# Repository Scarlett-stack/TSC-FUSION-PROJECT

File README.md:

# TSC-FUSION-PROJECT
Ebook project TSC 2025
## Schema bloc

## BOM
| Componentă                                 | Link sursă                                                                                          | Datasheet                                                                                          |
|--------------------------------------------|------------------------------------------------------------------------------------------------------|-----------------------------------------------------------------------------------------------------|
| BME680                                     | [SnapEDA](https://www.snapeda.com/parts/BME680/Bosch/view-part/?welcome=home)                      | [Datasheet](https://www.snapeda.com/parts/BME680/Bosch%20Sensortec/datasheet/)                    |
| CC0402MRX5R5BB106                          | [ComponentSearchEngine](https://componentsearchengine.com/part-view/CC0402MRX5R5BB106/YAGEO)       | [Datasheet](https://componentsearchengine.com/Datasheets/2/CC0402MRX5R5BB106.pdf)                 |
| DMG2305UX-7                                | [ComponentSearchEngine](https://componentsearchengine.com/part-view/DMG2305UX-7/Diodes%20Incorporated) | [Datasheet](https://www.diodes.com//assets/Datasheets/DMG2305UX.pdf)                              |
| Varistor B72520T0350K062                   | [Mouser](https://www.mouser.co.uk/ProductDetail/EPCOS-TDK/B72520T0350K062?qs=dEfas%2FXlABIszF52uu7vrg%3D%3D) | [Datasheet](https://www.tdk-electronics.tdk.com/inf/75/db/CTVS_14/Surge_protection_series.pdf)   |
| FH34SRJ-24S-0.5SH_99_                      | [ComponentSearchEngine](https://componentsearchengine.com/part-view/XC6220A331MR-G/Torex)          | [Datasheet](https://product.torexsemi.com/system/files/series/xc6220.pdf)                         |
| MAX17048G+T10                              | [SnapEDA](https://www.snapeda.com/parts/MAX17048G+T10/Analog+Devices/view-part/?ref=eda)           | [Datasheet](https://www.snapeda.com/parts/MAX17048G+T10/Analog%20Devices/datasheet/)              |
| MBR0530                                    | [Mouser](https://ro.mouser.com/ProductDetail/KYOCERA-AVX/SD0805S020S1R0?qs=jCA%252BPfw4LHbpkAoSnwrdjw%3D%3D) | [Datasheet](https://ro.mouser.com/datasheet/2/40/schottky-3165252.pdf)                            |
| PGB1010603MR                               | [SnapEDA](https://www.snapeda.com/parts/PGB1010603MR/Littelfuse/view-part/?ref=eda)                | [Datasheet](https://www.snapeda.com/parts/PGB1010603MR/Littelfuse%20Inc./datasheet/)              |
| TR3B106K025C1300                           | [Mouser](https://ro.mouser.com/ProductDetail/Vishay-Sprague/TR3B106K025C1300?qs=jCGqFXxTmLdffnuDkXzk1g%3D%3D) | [Datasheet](https://www.vishay.com/docs/40080/tr3.pdf)                                            |
| USB4110-GF-A                               | [ComponentSearchEngine](https://componentsearchengine.com/part-view/USB4110-GF-A/GCT%20(GLOBAL%20CONNECTOR%20TECHNOLOGY)) | [Datasheet](https://gct.co/files/drawings/usb4110.pdf)                                            |
| SI1308EDL-T1-GE3                           | [ComponentSearchEngine](https://componentsearchengine.com/part-view/SI1308EDL-T1-GE3/Vishay)       | [Datasheet](https://componentsearchengine.com/Datasheets/1/SI1308EDL-T1-GE3.pdf)                  |
| Solder Jumper (SJ)                         | [GrabCAD](https://grabcad.com/library/solder-jumpers-1)                                             | —                                                                                                  |
| USBLC6-2SC6Y                               | [SnapEDA](https://www.snapeda.com/parts/USBLC6-2SC6Y/STMicroelectronics/view-part/?ref=eda)        | [Datasheet](https://www.snapeda.com/parts/USBLC6-2SC6Y/STMicroelectronics/datasheet/)             |
| W25Q512JVEIQ                               | [SnapEDA](https://www.snapeda.com/parts/W25Q512JVEIQ/Winbond+Electronics/view-part/?ref=eda)       | [Datasheet](https://www.snapeda.com/parts/W25Q512JVEIQ/Winbond%20Electronics/datasheet/)          |
| XC6220A331MR-G                             | [ComponentSearchEngine](https://componentsearchengine.com/part-view/XC6220A331MR-G/Torex)          | [Datasheet](https://product.torexsemi.com/system/files/series/xc6220.pdf)                         |
| RC0402FR-07226RL                           | [SnapEDA](https://www.snapeda.com/parts/RC0402FR-07226RL/Yageo/view-part/)                         | [Datasheet](https://www.snapeda.com/parts/RC0402FR-07226RL/Yageo/datasheet/)                      |
| QWIIC PRT-14417                            | [SnapEDA](https://www.snapeda.com/parts/PRT-14417/SparkFun/view-part/)                             | [Datasheet](https://www.snapeda.com/parts/PRT-14417/SparkFun%20Electronics/datasheet/)            |
| BUTTON EVQPUJ02K                           | [Panasonic](https://industry.panasonic.com/global/en/downloads?tab=cad&small_g_cd=203&part_no=EVQPUJ02K) | [Datasheet](https://industry.panasonic.com/global/en/downloads?tab=catalog&small_g_cd=203&part_no=EVQPUJ02K) |
| CPH3225A                                   | [SnapEDA](https://www.snapeda.com/parts/CPH3225A/Seiko+Instruments/view-part/?ref=eda)             | [Datasheet](https://www.snapeda.com/parts/CPH3225A/Seiko%20Instruments/datasheet/)                |
| KP-1608SURCK (LED 0603)                    | [SnapEDA](https://www.snapeda.com/parts/KP-1608SURCK/Kingbright/view-part/?ref=search&t=LED%200603) | [Datasheet](https://www.snapeda.com/parts/KP-1608SURCK/Kingbright/datasheet/)                     |
| 112A-TAAR-R03_ATTEND                       | [Comet](https://store.comet.bg/en/Catalogue/Product/43497/)                                        | [Datasheet](https://store.comet.bg/en/Catalogue/Product/43497/)                                   |
| 744043680                                  | [DigiKey](https://www.digikey.sg/en/models/1638515)                                                 | [Datasheet](https://www.we-online.com/components/products/datasheet/744043680.pdf)                |
| BD5229G-TR                                 | [ComponentSearchEngine](https://componentsearchengine.com/part-view/BD5229G-TR/ROHM%20Semiconductor) | [Datasheet](https://datasheet.datasheetarchive.com/originals/distributors/Datasheets_SAMA/f2b9741ef86007909f138d561a359946.pdf) |
| DS3231SN#                                  | [SnapEDA](https://www.snapeda.com/parts/DS3231SN%23/Analog+Devices/view-part/?ref=eda)             | [Datasheet](https://www.snapeda.com/parts/DS3231SN%23/Analog%20Devices/datasheet/)                |
| ESP32-C6-WROOM-1-N8                        | [SnapEDA](https://www.snapeda.com/parts/ESP32-C6-WROOM-1-N8/Espressif+Systems/view-part/?ref=eda) | [Datasheet](https://www.snapeda.com/parts/ESP32-C6-WROOM-1-N8/Espressif%20Systems/datasheet/)     |
| MCP73831                                   | [DigiKey](https://www.digikey.com/en/models/1874108)                                                | —                                                                                                  |
## Conexiuni ESP32-C6

| Funcționalitate         | Pin ESP32-C6 | Descriere                                                  |
|-------------------------|--------------|-------------------------------------------------------------|
| UART pentru debug       | TX/RX        | Conectat la USB pentru programare si debug                 |
| I2C                     | IO4 (SCL), IO5 (SDA) | Utilizat pentru BME680, RTC și Qwiic connector            |
| SPI                     | IO10 (CLK), IO11 (MOSI), IO12 (MISO), IO13 (CS) | Conexiune la memorie flash și display e-paper            |
| Buton BOOT              | IO9          | Conectat la reset/supervisor                              |
| LED / Status            | IO6          | Indicator vizual                                           |
| GPIO-uri libere         | IO0, IO1, IO2, IO3 | Disponibile pentru extensii                               |

---

## Alimentare și Management Energie

- Alimentare principala: **3.7V Li-Po**
- Convertor LDO: **DMG2305UX** + **XC6220A331MR-G** — iesire 3.3V/300mA
- incarcare baterie: **MCP73831**
- Monitorizare baterie: **MAX17048**
- Protectie ESD: **USBLC6-2SC6Y** si protectii dedicate SPI

---

## Funcționalitate Hardware

- **ESP32-C6**: Procesor principal, suport Wi-Fi și BLE, interfata pentru toate componentele externe.
- **E-paper display**: Consum redusă.
- **Senzor de mediu BME680**: Citiri de temperatura, umiditate și calitate aer.
- **DS3231SN**: Ceas de timp real cu baterie de rezerva.
- **Memorie externă W25Q512JVEIQ**: 64MB pentru carti, setari etc.
- **MAX17048**: Estimare precisa a nivelului bateriei.
- **Interfete QWIIC / SPI / I2C** pentru extensibilitate și modularitate.

---

## Imagini PCB

Vezi folderul Images pt detalii

---

## Alte observații

- PCB-ul este în format Eagle, dimensiune compactă
- Conector USB-C cu protecții ESD
- Buton BOOT și RESET integrate
- Jumperi pentru configurare de test/debug
- Test Pads pentru depanare rapida

---
Am acceptat erorile SMD de overlap pt ca asa ni s-a zis la curs

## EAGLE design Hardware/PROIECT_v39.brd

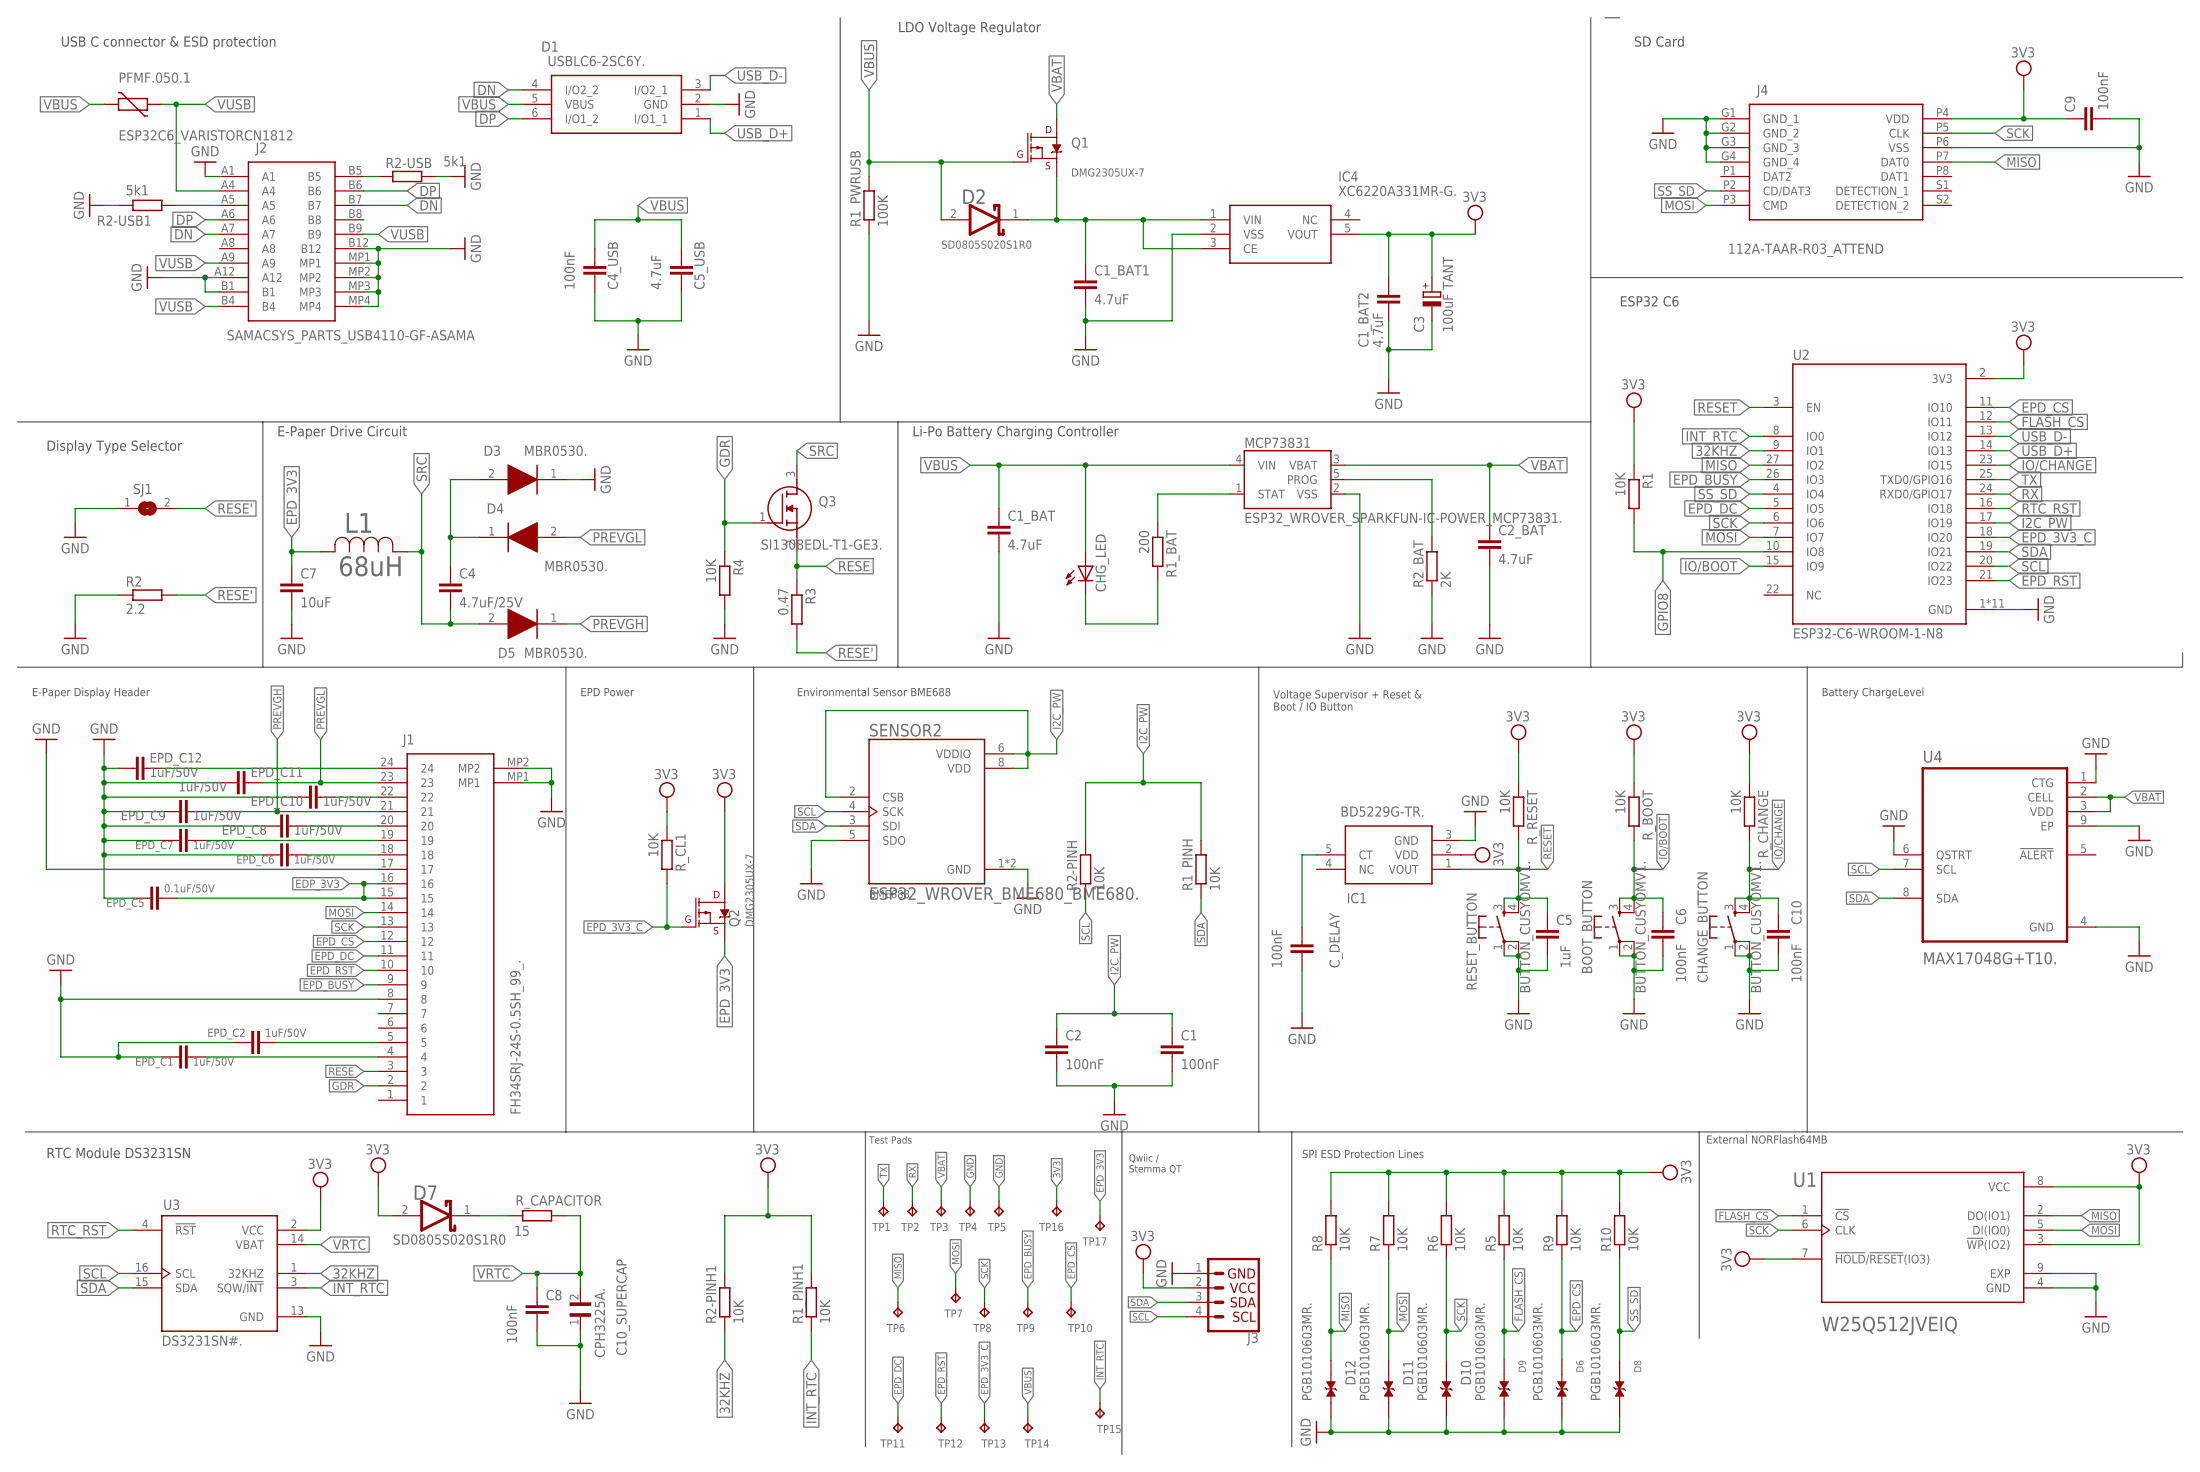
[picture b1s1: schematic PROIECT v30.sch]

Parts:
BOOT_BUTTON: BUTTON_CUSYOMV1.; MYBUTTON
C1, C2, C4_USB, C6, C8, C9, C10: 100nF; EAGLE-LTSPICE_C0402
C1_BAT, C1_BAT1, C1_BAT2, C2_BAT, C5_USB: 4.7uF; EAGLE-LTSPICE_C0402
C3: 100uF TANT; RCL_CT3528
C4: 4.7uF/25V; EAGLE-LTSPICE_C0402
C5: 1uF; EAGLE-LTSPICE_C0402
C7: 10uF; EAGLE-LTSPICE_C0402
C10_SUPERCAP: CPH3225A.; CAPCP3225X100N
CHANGE_BUTTON: BUTTON_CUSYOMV1.; MYBUTTON
CHG_LED: ADAFRUIT_LEDCHIP-LED0603; ADAFRUIT_CHIP-LED0603
C_DELAY: 100nF; EAGLE-LTSPICE_C0402
D1: USBLC6-2SC6Y.; SOT95P280X145-6N
D2, D7: ESP32_WROVER_AVX---SD0805S020S1R0_AVX_SD0805S020S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; ESP32_WROVER_AVX---SD0805S020S1R0_AVX_SD0805S020S1R0_0
D3, D4, D5: MBR0530.; SOD3716X135N
D6, D8, D9, D10, D11, D12: PGB1010603MR.; DIOC1608X36N
EPD_C1, EPD_C2, EPD_C6, EPD_C7, EPD_C8, EPD_C9, EPD_C10, EPD_C11, EPD_C12: 1uF/50V; EAGLE-LTSPICE_C0402
EPD_C5: 0.1uF/50V; EAGLE-LTSPICE_C0402
IC1: BD5229G-TR.; SOT95P280X125-5N
IC4: XC6220A331MR-G.; SOT95P280X120-5N
J1: FH34SRJ-24S-0.5SH_99_.; FH34SRJ24S05SH99
J2: SAMACSYS_PARTS_USB4110-GF-ASAMA; SAMACSYS_PARTS_USB4110GFA
J3: QWIIC_RIGHT_ANGLE; JST04_1MM_RA
J4: 112A-TAAR-R03_ATTEND; 112ATAARR03ATTEND
L1: 68uH; IND_4828-WE-TPC_WRE
MCP73831: ESP32_WROVER_SPARKFUN-IC-POWER_MCP73831.; ESP32_WROVER_SPARKFUN-IC-POWER_SOT23-5
PFMF.050.1: ESP32C6_VARISTORCN1812; ESP32C6_VARISTOR_CT/CN1812
Q1, Q2: 20V/4.2A/52mΩ/1.4W; ESP32_WROVER_SPARKFUN-DISCRETESEMI_SOT23-3
Q3: SI1308EDL-T1-GE3.; SOT65P210X110-3N
R1, R1_PINH, R1_PINH1, R2-PINH, R2-PINH1, R4, R5, R6, R7, R8, R9, R10: 10K; ESP32_WROVER_EAGLE-LTSPICE_R0402
R1_BAT: 200; ESP32_WROVER_EAGLE-LTSPICE_R0402
R1_PWRUSB: 100K; ESP32_WROVER_EAGLE-LTSPICE_R0402
R2: 2.2; ESP32_WROVER_EAGLE-LTSPICE_R0402
R2-USB, R2-USB1: 5k1; ESP32_WROVER_EAGLE-LTSPICE_R0402
R2_BAT: 2K; ESP32_WROVER_EAGLE-LTSPICE_R0402
R3: 0.47; ESP32_WROVER_EAGLE-LTSPICE_R0402
RESET_BUTTON: BUTTON_CUSYOMV1.; MYBUTTON
R_BOOT: 10K; ESP32_WROVER_EAGLE-LTSPICE_R0402
R_CAPACITOR: 15; ESP32_WROVER_EAGLE-LTSPICE_R0402
R_CHANGE: 10K; ESP32_WROVER_EAGLE-LTSPICE_R0402
R_CL1: 10K; ESP32_WROVER_EAGLE-LTSPICE_R0402
R_RESET: 10K; ESP32_WROVER_EAGLE-LTSPICE_R0402
SENSOR2: ESP32_WROVER_BME680_BME680.; ESP32_WROVER_BME680_PSON80P300X300X100-8N
SJ1: SJ.; SJ
TP1, TP2, TP3, TP4, TP5, TP6, TP7, TP8, TP9, TP10, TP11, TP12, TP13, TP14, TP15, TP16, TP17: TPTP20R; TP20R
U1: W25Q512JVEIQ; SON127P600X800X80-9N
U2: ESP32-C6-WROOM-1-N8; XCVR_ESP32-C6-WROOM-1-N8
U3: DS3231SN#.; SOIC127P1032X265-16N
U4: MAX17048G+T10.; SON50P200X200X80-9N

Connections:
3V3: C1_BAT2.1, C3.+, C9.1, D7.2 (ANODE), IC1.2 (VDD), IC4.5 (VOUT), J3.2, J4.P4 (VDD), Q2.3 (D), R1.1, R1_PINH1.2, R2-PINH1.2, R5.2, R6.2, R7.2, R8.2, R9.2, R10.2, R_BOOT.1, R_CHANGE.1, R_CL1.1, R_RESET.1, TP16.TP, U1.3 (!WP!(IO2)), U1.7 (!HOLD!/!RESET!(IO3)), U1.8 (VCC), U2.2 (3V3), U3.2 (VCC)
32KHZ: R2-PINH1.1, U2.9 (IO1), U3.1 (32KHZ)
DN: D1.4 (I/O2_2), J2.A7, J2.B7
DP: D1.6 (I/O1_2), J2.A6, J2.B6
EDP_3V3: EPD_C5.1, J1.15, J1.16
EPD_3V3: C7.1, L1.2, Q2.2 (S), TP17.TP
EPD_3V3_C: Q2.1 (G), R_CL1.2, TP13.TP, U2.18 (IO20)
EPD_BUSY: J1.9, TP9.TP, U2.26 (IO3)
EPD_CS: D6.1, J1.12, R9.1, TP10.TP, U2.11 (IO10)
EPD_DC: J1.11, TP11.TP, U2.5 (IO5)
EPD_RST: J1.10, TP12.TP, U2.21 (IO23)
FLASH_CS: D9.1, R5.1, U1.1 (!CS), U2.12 (IO11)
GDR: J1.2, Q3.1 (G), R4.1
GND: BOOT_BUTTON.1, BOOT_BUTTON.2, C1.2, C1_BAT.2, C1_BAT1.2, C1_BAT2.2, C2.2, C2_BAT.2, C3.-, C4_USB.2, C5.2, C5_USB.2, C6.2, C7.2, C8.2, C9.2, C10.2, C10_SUPERCAP.1, CHANGE_BUTTON.1, CHANGE_BUTTON.2, C_DELAY.2, D1.2 (GND), D3.1 (K), D6.2, D8.2, D9.2, D10.2, D11.2, D12.2, EPD_C1.2, EPD_C2.2, EPD_C5.2, EPD_C6.2, EPD_C7.2, EPD_C8.2, EPD_C9.2, EPD_C10.2, EPD_C11.2, EPD_C12.2, IC1.3 (GND), IC4.2 (VSS), J1.8, J1.17, J1.MP1, J1.MP2, J2.A1, J2.A12, J2.B1, J2.B12, J2.MP1, J2.MP2, J2.MP3, J2.MP4, J3.1, J4.G1 (GND_1), J4.G2 (GND_2), J4.G3 (GND_3), J4.G4 (GND_4), J4.P6 (VSS), MCP73831.2 (VSS), R1_PWRUSB.1, R2.1, R2-USB.2, R2-USB1.1, R2_BAT.1, R4.2, RESET_BUTTON.1, RESET_BUTTON.2, SENSOR2.1 (GND), SENSOR2.5 (SDO), SENSOR2.7 (GND), SJ1.1, TP4.TP, TP5.TP, U1.4 (GND), U1.9 (EXP), U2.1 (GND), U2.28 (GND), U2.29_1 (GND), U2.29_2 (GND), U2.29_3 (GND), U2.29_4 (GND), U2.29_5 (GND), U2.29_6 (GND), U2.29_7 (GND), U2.29_8 (GND), U2.29_9 (GND), U3.13 (GND), U4.1 (CTG), U4.4 (GND), U4.6 (QSTRT), U4.9 (EP)
GPIO8: R1.2, U2.10 (IO8)
I2C_PW: C1.1, C2.1, R1_PINH.2, R2-PINH.2, SENSOR2.2 (CSB), SENSOR2.6 (VDDIO), SENSOR2.8 (VDD), U2.17 (IO19)
INT_RTC: R1_PINH1.1, TP15.TP, U2.8 (IO0), U3.3 (SQW/!INT)
IO/BOOT: BOOT_BUTTON.3, BOOT_BUTTON.4, C6.1, R_BOOT.2, U2.15 (IO9)
IO/CHANGE: C10.1, CHANGE_BUTTON.3, CHANGE_BUTTON.4, R_CHANGE.2, U2.23 (IO15)
MISO: D12.1, J4.P7 (DAT0), R8.1, TP6.TP, U1.2 (DO(IO1)), U2.27 (IO2)
MOSI: D11.1, J1.14, J4.P3 (CMD), R7.1, TP7.TP, U1.5 (DI(IO0)), U2.7 (IO7)
unnamed: C1_BAT1.1, D2.1 (CATHODE), IC4.1 (VIN), IC4.3 (CE), Q1.2 (S)
unnamed: CHG_LED.C, R1_BAT.2
unnamed: MCP73831.1 (STAT), R1_BAT.1
unnamed: J2.A5, R2-USB1.2
unnamed: C4.1, D3.2 (A), D4.1 (K)
unnamed: EPD_C12.1, J1.24
unnamed: MCP73831.5 (PROG), R2_BAT.2
unnamed: EPD_C10.1, J1.22
unnamed: C_DELAY.1, IC1.5 (CT)
unnamed: EPD_C8.1, J1.20
unnamed: J2.B5, R2-USB.1
unnamed: EPD_C7.1, J1.19
unnamed: EPD_C6.1, J1.18
unnamed: EPD_C2.1, J1.5
unnamed: EPD_C1.1, J1.4
unnamed: D7.1 (CATHODE), R_CAPACITOR.2
PREVGH: D5.1 (K), EPD_C9.1, J1.21
PREVGL: D4.2 (A), EPD_C11.1, J1.23
RESE: J1.3, Q3.2 (S), R3.1
RESE': R2.2, R3.2, SJ1.2
RESET: C5.1, IC1.1 (VOUT), RESET_BUTTON.3, RESET_BUTTON.4, R_RESET.2, U2.3 (EN)
RTC_RST: U2.16 (IO18), U3.4 (!RST)
RX: TP2.TP, U2.24 (RXD0/GPIO17)
SCK: D10.1, J1.13, J4.P5 (CLK), R6.1, TP8.TP, U1.6 (CLK), U2.6 (IO6)
SCL: J3.4, R2-PINH.1, SENSOR2.4 (SCK), U2.20 (IO22), U3.16 (SCL), U4.7 (SCL)
SDA: J3.3, R1_PINH.1, SENSOR2.3 (SDI), U2.19 (IO21), U3.15 (SDA), U4.8 (SDA)
SRC: C4.2, D5.2 (A), L1.1, Q3.3 (D)
SS_SD: D8.1, J4.P2 (CD/DAT3), R10.1, U2.4 (IO4)
TX: TP1.TP, U2.25 (TXD0/GPIO16)
USB_D+: D1.1 (I/O1_1), U2.14 (IO13)
USB_D-: D1.3 (I/O2_1), U2.13 (IO12)
VBAT: C2_BAT.1, MCP73831.3 (VBAT), Q1.3 (D), TP3.TP, U4.2 (CELL), U4.3 (VDD)
VBUS: C1_BAT.1, C4_USB.1, C5_USB.1, CHG_LED.A, D1.5 (VBUS), D2.2 (ANODE), MCP73831.4 (VIN), PFMF.050.1.2, Q1.1 (G), R1_PWRUSB.2, TP14.TP
VRTC: C8.1, C10_SUPERCAP.2, R_CAPACITOR.1, U3.14 (VBAT)
VUSB: J2.A4, J2.A9, J2.B4, J2.B9, PFMF.050.1.1

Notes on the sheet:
SD Card
ESP32 C6
USB C connector & ESD protection
Display Type Selector
LDO Voltage Regulator
E-Paper Drive Circuit
Li-Po Battery Charging Controller
E-Paper Display Header
EPD Power
Environmental Sensor BME688
Voltage Supervisor + Reset & Boot / IO Button
Battery ChargeLevel
RTC Module DS3231SN
Test Pads
Qwiic / Stemma QT
SPI ESD Protection Lines
External NORFlash64MB

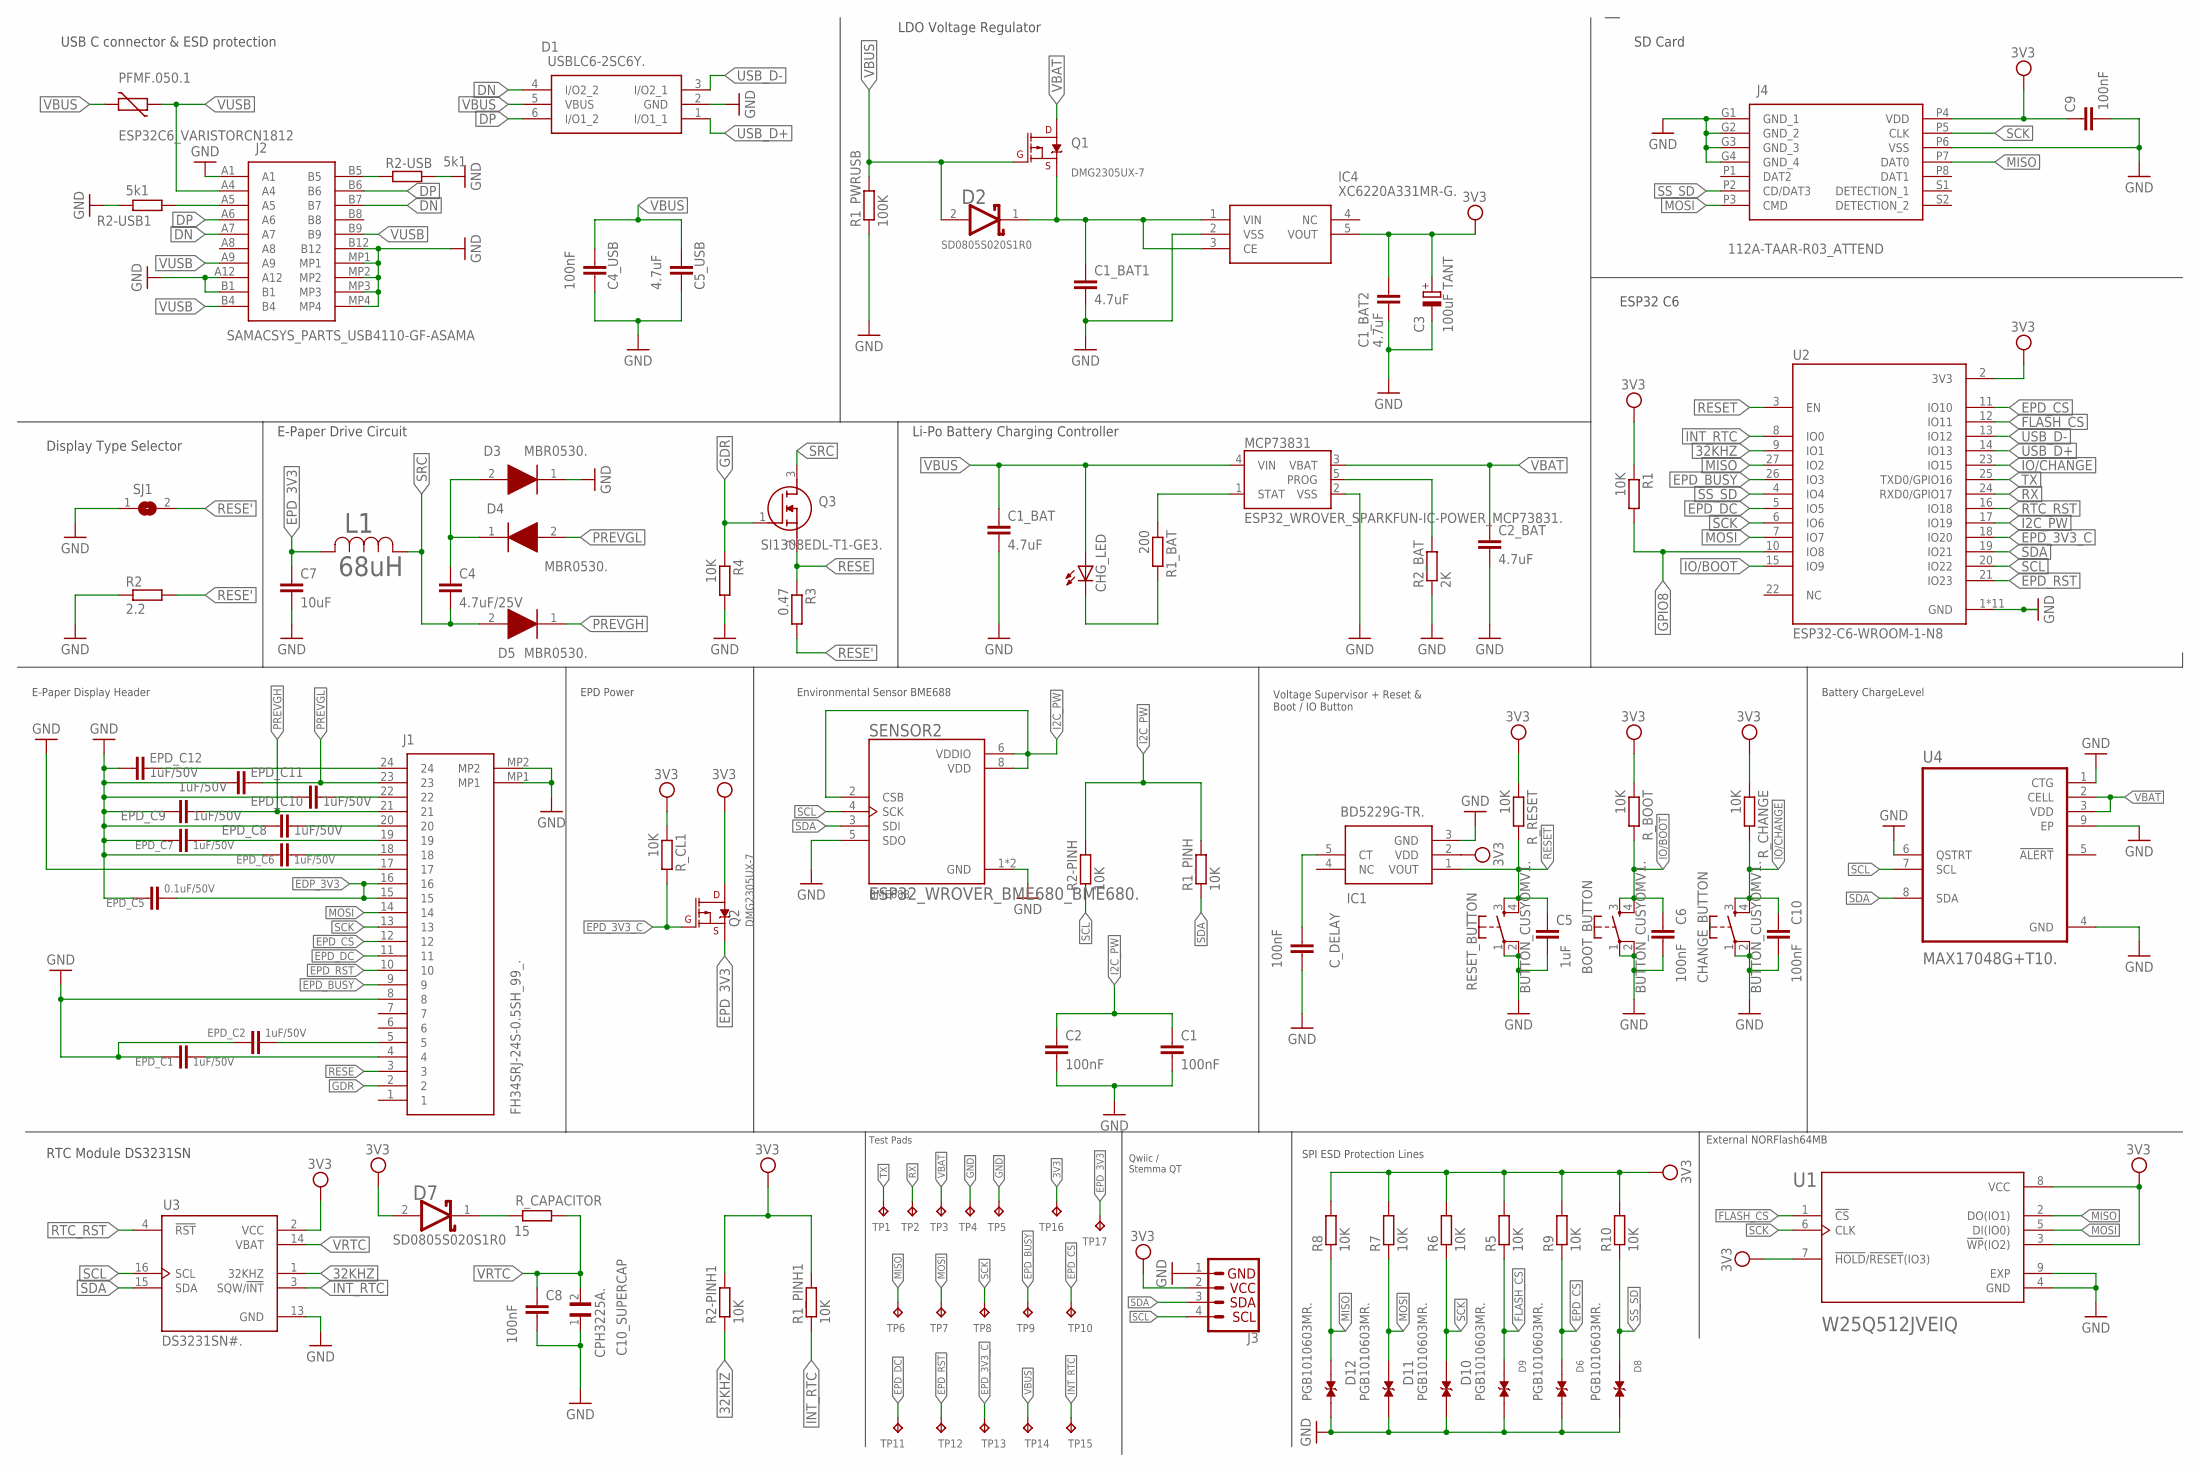
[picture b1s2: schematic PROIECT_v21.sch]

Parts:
BOOT_BUTTON: BUTTON_CUSYOMV1.; MYBUTTON
C1, C2, C4_USB, C6, C8, C9, C10: 100nF; EAGLE-LTSPICE_C0402
C1_BAT, C1_BAT1, C1_BAT2, C2_BAT, C5_USB: 4.7uF; EAGLE-LTSPICE_C0402
C3: 100uF TANT; RCL_CT3528
C4: 4.7uF/25V; EAGLE-LTSPICE_C0402
C5: 1uF; EAGLE-LTSPICE_C0402
C7: 10uF; EAGLE-LTSPICE_C0402
C10_SUPERCAP: CPH3225A.; CAPCP3225X100N
CHANGE_BUTTON: BUTTON_CUSYOMV1.; MYBUTTON
CHG_LED: ADAFRUIT_LEDCHIP-LED0603; ADAFRUIT_CHIP-LED0603
C_DELAY: 100nF; EAGLE-LTSPICE_C0402
D1: USBLC6-2SC6Y.; SOT95P280X145-6N
D2, D7: ESP32_WROVER_AVX---SD0805S020S1R0_AVX_SD0805S020S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; ESP32_WROVER_AVX---SD0805S020S1R0_AVX_SD0805S020S1R0_0
D3, D4, D5: MBR0530.; SOD3716X135N
D6, D8, D9, D10, D11, D12: PGB1010603MR.; DIOC1608X36N
EPD_C1, EPD_C2, EPD_C6, EPD_C7, EPD_C8, EPD_C9, EPD_C10, EPD_C11, EPD_C12: 1uF/50V; EAGLE-LTSPICE_C0402
EPD_C5: 0.1uF/50V; EAGLE-LTSPICE_C0402
IC1: BD5229G-TR.; SOT95P280X125-5N
IC4: XC6220A331MR-G.; SOT95P280X120-5N
J1: FH34SRJ-24S-0.5SH_99_.; FH34SRJ24S05SH99
J2: SAMACSYS_PARTS_USB4110-GF-ASAMA; SAMACSYS_PARTS_USB4110GFA
J3: QWIIC_RIGHT_ANGLE; JST04_1MM_RA
J4: 112A-TAAR-R03_ATTEND; 112ATAARR03ATTEND
L1: 68uH; IND_4828-WE-TPC_WRE
MCP73831: ESP32_WROVER_SPARKFUN-IC-POWER_MCP73831.; ESP32_WROVER_SPARKFUN-IC-POWER_SOT23-5
PFMF.050.1: ESP32C6_VARISTORCN1812; ESP32C6_VARISTOR_CT/CN1812
Q1, Q2: 20V/4.2A/52mΩ/1.4W; ESP32_WROVER_SPARKFUN-DISCRETESEMI_SOT23-3
Q3: SI1308EDL-T1-GE3.; SOT65P210X110-3N
R1, R1_PINH, R1_PINH1, R2-PINH, R2-PINH1, R4, R5, R6, R7, R8, R9, R10: 10K; ESP32_WROVER_EAGLE-LTSPICE_R0402
R1_BAT: 200; ESP32_WROVER_EAGLE-LTSPICE_R0402
R1_PWRUSB: 100K; ESP32_WROVER_EAGLE-LTSPICE_R0402
R2: 2.2; ESP32_WROVER_EAGLE-LTSPICE_R0402
R2-USB, R2-USB1: 5k1; ESP32_WROVER_EAGLE-LTSPICE_R0402
R2_BAT: 2K; ESP32_WROVER_EAGLE-LTSPICE_R0402
R3: 0.47; ESP32_WROVER_EAGLE-LTSPICE_R0402
RESET_BUTTON: BUTTON_CUSYOMV1.; MYBUTTON
R_BOOT: 10K; ESP32_WROVER_EAGLE-LTSPICE_R0402
R_CAPACITOR: 15; ESP32_WROVER_EAGLE-LTSPICE_R0402
R_CHANGE: 10K; ESP32_WROVER_EAGLE-LTSPICE_R0402
R_CL1: 10K; ESP32_WROVER_EAGLE-LTSPICE_R0402
R_RESET: 10K; ESP32_WROVER_EAGLE-LTSPICE_R0402
SENSOR2: ESP32_WROVER_BME680_BME680.; ESP32_WROVER_BME680_PSON80P300X300X100-8N
SJ1: SJ.; SJ
TP1, TP2, TP3, TP4, TP5, TP6, TP7, TP8, TP9, TP10, TP11, TP12, TP13, TP14, TP15, TP16, TP17: TPTP20R; TP20R
U1: W25Q512JVEIQ; SON127P600X800X80-9N
U2: ESP32-C6-WROOM-1-N8; XCVR_ESP32-C6-WROOM-1-N8
U3: DS3231SN#.; SOIC127P1032X265-16N
U4: MAX17048G+T10.; SON50P200X200X80-9N

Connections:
3V3: C1_BAT2.1, C3.+, C9.1, D7.2 (ANODE), IC1.2 (VDD), IC4.5 (VOUT), J3.2, J4.P4 (VDD), Q2.3 (D), R1.1, R1_PINH1.2, R2-PINH1.2, R5.2, R6.2, R7.2, R8.2, R9.2, R10.2, R_BOOT.1, R_CHANGE.1, R_CL1.1, R_RESET.1, TP16.TP, U1.3 (!WP!(IO2)), U1.7 (!HOLD!/!RESET!(IO3)), U1.8 (VCC), U2.2 (3V3), U3.2 (VCC)
32KHZ: R2-PINH1.1, U2.9 (IO1), U3.1 (32KHZ)
DN: D1.4 (I/O2_2), J2.A7, J2.B7
DP: D1.6 (I/O1_2), J2.A6, J2.B6
EDP_3V3: EPD_C5.1, J1.15, J1.16
EPD_3V3: C7.1, L1.2, Q2.2 (S), TP17.TP
EPD_3V3_C: Q2.1 (G), R_CL1.2, TP13.TP, U2.18 (IO20)
EPD_BUSY: J1.9, TP9.TP, U2.26 (IO3)
EPD_CS: D6.1, J1.12, R9.1, TP10.TP, U2.11 (IO10)
EPD_DC: J1.11, TP11.TP, U2.5 (IO5)
EPD_RST: J1.10, TP12.TP, U2.21 (IO23)
FLASH_CS: D9.1, R5.1, U1.1 (!CS), U2.12 (IO11)
GDR: J1.2, Q3.1 (G), R4.1
GND: BOOT_BUTTON.1, BOOT_BUTTON.2, C1.2, C1_BAT.2, C1_BAT1.2, C1_BAT2.2, C2.2, C2_BAT.2, C3.-, C4_USB.2, C5.2, C5_USB.2, C6.2, C7.2, C8.2, C9.2, C10.2, C10_SUPERCAP.1, CHANGE_BUTTON.1, CHANGE_BUTTON.2, C_DELAY.2, D1.2 (GND), D3.1 (K), D6.2, D8.2, D9.2, D10.2, D11.2, D12.2, EPD_C1.2, EPD_C2.2, EPD_C5.2, EPD_C6.2, EPD_C7.2, EPD_C8.2, EPD_C9.2, EPD_C10.2, EPD_C11.2, EPD_C12.2, IC1.3 (GND), IC4.2 (VSS), J1.8, J1.17, J1.MP1, J1.MP2, J2.A1, J2.A12, J2.B1, J2.B12, J2.MP1, J2.MP2, J2.MP3, J2.MP4, J3.1, J4.G1 (GND_1), J4.G2 (GND_2), J4.G3 (GND_3), J4.G4 (GND_4), J4.P6 (VSS), MCP73831.2 (VSS), R1_PWRUSB.1, R2.1, R2-USB.2, R2-USB1.1, R2_BAT.1, R4.2, RESET_BUTTON.1, RESET_BUTTON.2, SENSOR2.1 (GND), SENSOR2.5 (SDO), SENSOR2.7 (GND), SJ1.1, TP4.TP, TP5.TP, U1.4 (GND), U1.9 (EXP), U2.1 (GND), U2.28 (GND), U2.29_1 (GND), U2.29_2 (GND), U2.29_3 (GND), U2.29_4 (GND), U2.29_5 (GND), U2.29_6 (GND), U2.29_7 (GND), U2.29_8 (GND), U2.29_9 (GND), U3.13 (GND), U4.1 (CTG), U4.4 (GND), U4.6 (QSTRT), U4.9 (EP)
GPIO8: R1.2, U2.10 (IO8)
I2C_PW: C1.1, C2.1, R1_PINH.2, R2-PINH.2, SENSOR2.2 (CSB), SENSOR2.6 (VDDIO), SENSOR2.8 (VDD), U2.17 (IO19)
INT_RTC: R1_PINH1.1, TP15.TP, U2.8 (IO0), U3.3 (SQW/!INT)
IO/BOOT: BOOT_BUTTON.3, BOOT_BUTTON.4, C6.1, R_BOOT.2, U2.15 (IO9)
IO/CHANGE: C10.1, CHANGE_BUTTON.3, CHANGE_BUTTON.4, R_CHANGE.2, U2.23 (IO15)
MISO: D12.1, J4.P7 (DAT0), R8.1, TP6.TP, U1.2 (DO(IO1)), U2.27 (IO2)
MOSI: D11.1, J1.14, J4.P3 (CMD), R7.1, TP7.TP, U1.5 (DI(IO0)), U2.7 (IO7)
unnamed: C1_BAT1.1, D2.1 (CATHODE), IC4.1 (VIN), IC4.3 (CE), Q1.2 (S)
unnamed: CHG_LED.C, R1_BAT.2
unnamed: MCP73831.1 (STAT), R1_BAT.1
unnamed: J2.A5, R2-USB1.2
unnamed: C4.1, D3.2 (A), D4.1 (K)
unnamed: EPD_C12.1, J1.24
unnamed: MCP73831.5 (PROG), R2_BAT.2
unnamed: EPD_C10.1, J1.22
unnamed: C_DELAY.1, IC1.5 (CT)
unnamed: EPD_C8.1, J1.20
unnamed: J2.B5, R2-USB.1
unnamed: EPD_C7.1, J1.19
unnamed: EPD_C6.1, J1.18
unnamed: EPD_C2.1, J1.5
unnamed: EPD_C1.1, J1.4
unnamed: D7.1 (CATHODE), R_CAPACITOR.2
PREVGH: D5.1 (K), EPD_C9.1, J1.21
PREVGL: D4.2 (A), EPD_C11.1, J1.23
RESE: J1.3, Q3.2 (S), R3.1
RESE': R2.2, R3.2, SJ1.2
RESET: C5.1, IC1.1 (VOUT), RESET_BUTTON.3, RESET_BUTTON.4, R_RESET.2, U2.3 (EN)
RTC_RST: U2.16 (IO18), U3.4 (!RST)
RX: TP2.TP, U2.24 (RXD0/GPIO17)
SCK: D10.1, J1.13, J4.P5 (CLK), R6.1, TP8.TP, U1.6 (CLK), U2.6 (IO6)
SCL: J3.4, R2-PINH.1, SENSOR2.4 (SCK), U2.20 (IO22), U3.16 (SCL), U4.7 (SCL)
SDA: J3.3, R1_PINH.1, SENSOR2.3 (SDI), U2.19 (IO21), U3.15 (SDA), U4.8 (SDA)
SRC: C4.2, D5.2 (A), L1.1, Q3.3 (D)
SS_SD: D8.1, J4.P2 (CD/DAT3), R10.1, U2.4 (IO4)
TX: TP1.TP, U2.25 (TXD0/GPIO16)
USB_D+: D1.1 (I/O1_1), U2.14 (IO13)
USB_D-: D1.3 (I/O2_1), U2.13 (IO12)
VBAT: C2_BAT.1, MCP73831.3 (VBAT), Q1.3 (D), TP3.TP, U4.2 (CELL), U4.3 (VDD)
VBUS: C1_BAT.1, C4_USB.1, C5_USB.1, CHG_LED.A, D1.5 (VBUS), D2.2 (ANODE), MCP73831.4 (VIN), PFMF.050.1.2, Q1.1 (G), R1_PWRUSB.2, TP14.TP
VRTC: C8.1, C10_SUPERCAP.2, R_CAPACITOR.1, U3.14 (VBAT)
VUSB: J2.A4, J2.A9, J2.B4, J2.B9, PFMF.050.1.1

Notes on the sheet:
SD Card
ESP32 C6
USB C connector & ESD protection
Display Type Selector
LDO Voltage Regulator
E-Paper Drive Circuit
Li-Po Battery Charging Controller
E-Paper Display Header
EPD Power
Environmental Sensor BME688
Voltage Supervisor + Reset & Boot / IO Button
Battery ChargeLevel
RTC Module DS3231SN
Test Pads
Qwiic / Stemma QT
SPI ESD Protection Lines
External NORFlash64MB

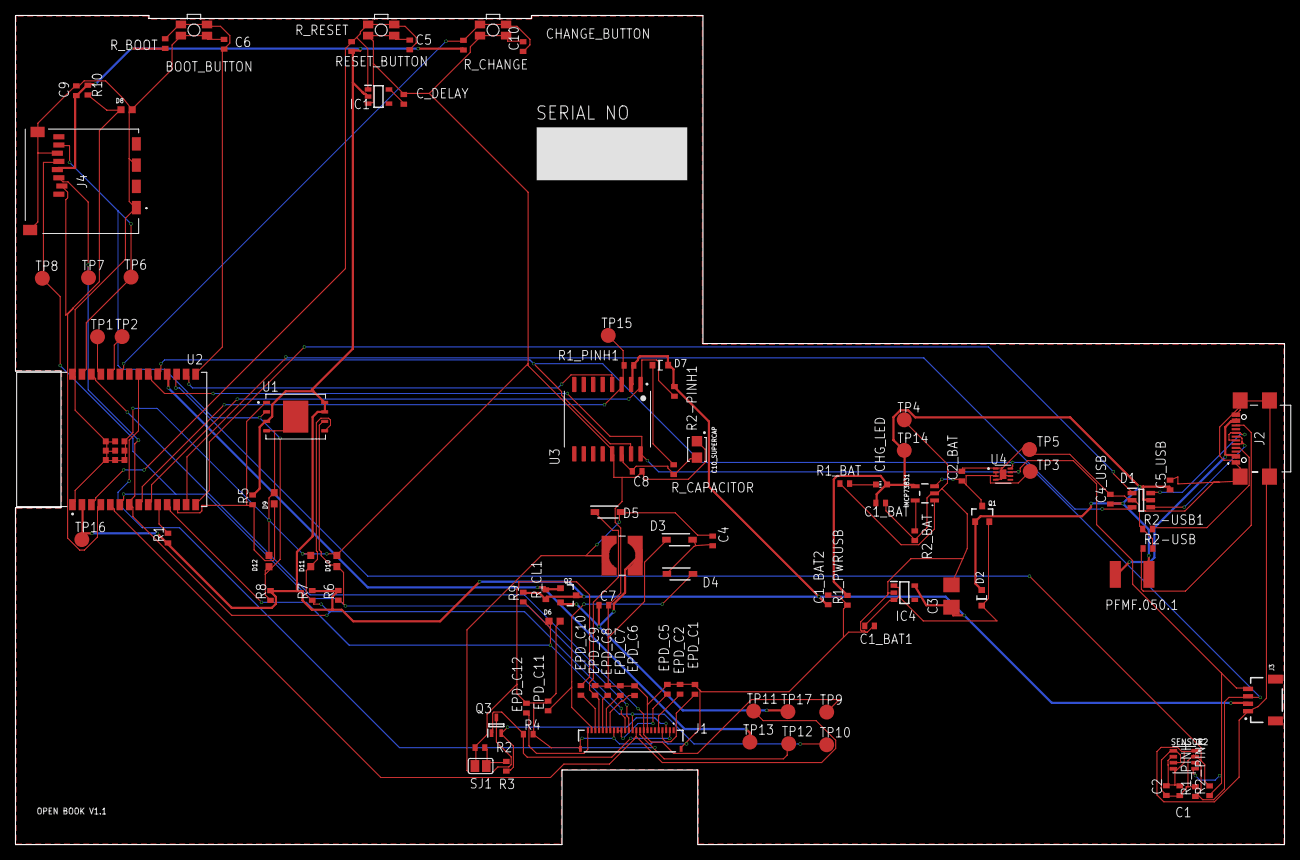
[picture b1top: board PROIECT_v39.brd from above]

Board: 2 copper layers, 170.2 x 111.2 mm, 103 parts (0 on the bottom side), 56 nets.

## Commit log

2025-04-06 Create LICENSE
2025-04-16 brd solved
2025-04-16 schematic
